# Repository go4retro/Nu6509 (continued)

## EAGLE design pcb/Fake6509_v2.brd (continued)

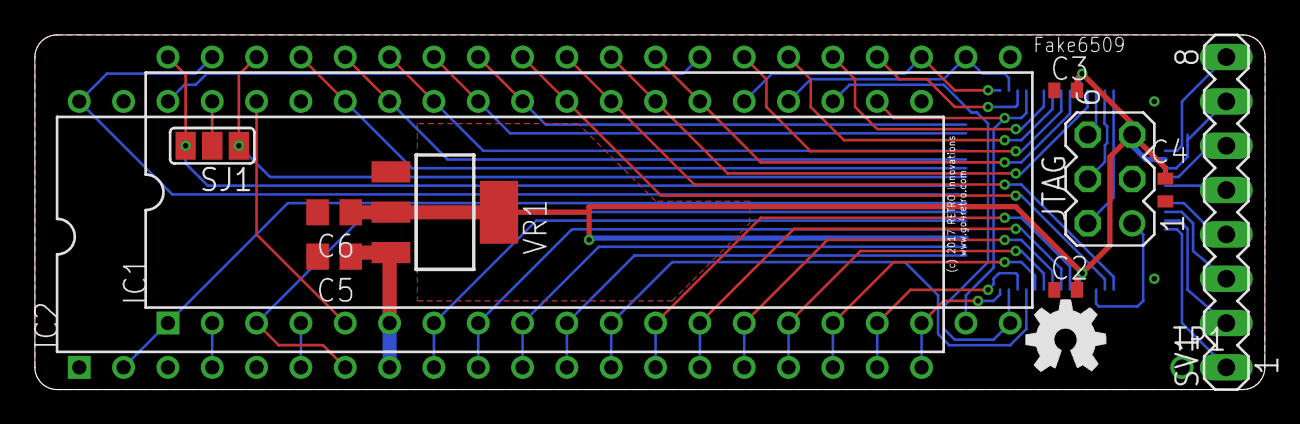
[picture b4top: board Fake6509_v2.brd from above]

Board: 2 copper layers, 70.5 x 20.3 mm, 14 parts (1 on the bottom side), 54 nets.

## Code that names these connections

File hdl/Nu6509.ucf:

#PACE: Start of Constraints generated by PACE

#PACE: Start of PACE I/O Pin Assignments
NET "_abort"  LOC = "P32"  ;
NET "be"  LOC = "P33"  ;
NET "_rdy"  LOC = "P25"  ; 
NET "_reset"  LOC = "P56"  ;
NET "_so"  LOC = "P40"  ;
NET "address_6502<0>"  LOC = "P24"  ; 
NET "address_6502<10>"  LOC = "P12"  ; 
NET "address_6502<11>"  LOC = "P11"  ; 
NET "address_6502<12>"  LOC = "P10"  ; 
NET "address_6502<13>"  LOC = "P8"  ; 
NET "address_6502<14>"  LOC = "P9"  ; 
NET "address_6502<15>"  LOC = "P7"  ; 
NET "address_6502<1>"  LOC = "P23"  ; 
NET "address_6502<2>"  LOC = "P22"  ; 
NET "address_6502<3>"  LOC = "P20"  ; 
NET "address_6502<4>"  LOC = "P19"  ; 
NET "address_6502<5>"  LOC = "P18"  ; 
NET "address_6502<6>"  LOC = "P17"  ; 
NET "address_6502<7>"  LOC = "P16"  ; 
NET "address_6502<8>"  LOC = "P15"  ; 
NET "address_6502<9>"  LOC = "P13"  ; 
NET "address_bank<0>"  LOC = "P38"  ;
NET "address_bank<1>"  LOC = "P2"  ; 
NET "address_bank<2>"  LOC = "P5"  ; 
NET "address_bank<3>"  LOC = "P6"  ; 
NET "address_bank<4>"  LOC = "P43"  ;
NET "address_bank<5>"  LOC = "P36"  ;
NET "address_bank<6>"  LOC = "P35"  ;
NET "address_bank<7>"  LOC = "P34"  ;
NET "data_6502<0>"  LOC = "P63"  ; 
NET "data_6502<1>"  LOC = "P49"  ;
NET "data_6502<2>"  LOC = "P47"  ;
NET "data_6502<3>"  LOC = "P45"  ;
NET "data_6502<4>"  LOC = "P42"  ;
NET "data_6502<5>"  LOC = "P39"  ;
NET "data_6502<6>"  LOC = "P1"  ; 
NET "data_6502<7>"  LOC = "P4"  ; 
NET "data_6509<0>"  LOC = "P52"  ;
NET "data_6509<1>"  LOC = "P59"  ; 
NET "data_6509<2>"  LOC = "P61"  ; 
NET "data_6509<3>"  LOC = "P62"  ; 
NET "data_6509<4>"  LOC = "P64"  ; 
NET "data_6509<5>"  LOC = "P48"  ;
NET "data_6509<6>"  LOC = "P46"  ;
NET "data_6509<7>"  LOC = "P44"  ;
NET "e"  LOC = "P60"  ; 
NET "mx"  LOC = "P58"  ;
NET "phi2_6509"  LOC = "P50"  ;
NET "r_w"  LOC = "P51"  ;
NET "sync"  LOC = "P27"  ; 
NET "vda"  LOC = "P57"  ;
NET "vpa"  LOC = "P31"  ; 

#PACE: Start of PACE Area Constraints

#PACE: Start of PACE Prohibit Constraints

#PACE: End of Constraints generated by PACE

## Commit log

2018-02-21 Added Flowerbox to Fask6509.v
2018-02-24 Added comments to Verilog and cleaned up a small bug in the PCB
2018-02-25 More changes to Verilog and PCB cleanup
2018-02-25 Added PDFs of Schematic and PCB
2018-02-28 Reference Timing Information
2018-03-01 Simplified Verilog and changed clock signal (PHI1 and PHI2 are misnamed on the datasheet)
2018-03-03 Created v3 of PCB
2018-03-11 Added license
2018-03-11 Updated license files
2018-06-29 Bank read needs to stay active until address lines change, not just until clock goes low.
2018-06-29 v3 HDL
2018-06-29 Added traces for Rockwell 65C02
2018-06-29 NMOS 6502 Traces
2018-07-28 Cleanup
2018-07-28 Modify PCB and Verilog to support both '02 and '816
2019-04-15 Add in '816 support
2019-04-15 Added Michal Pleban's test.d80
2019-04-15 .gitignore additions
2019-04-19 Disabled writes to $0 and $1 when in 816 native mode and fixed copyright notice
2019-10-03 Updated .gitignore
2019-12-05 Switch name to Nu6509
2020-04-17 Added JED file
